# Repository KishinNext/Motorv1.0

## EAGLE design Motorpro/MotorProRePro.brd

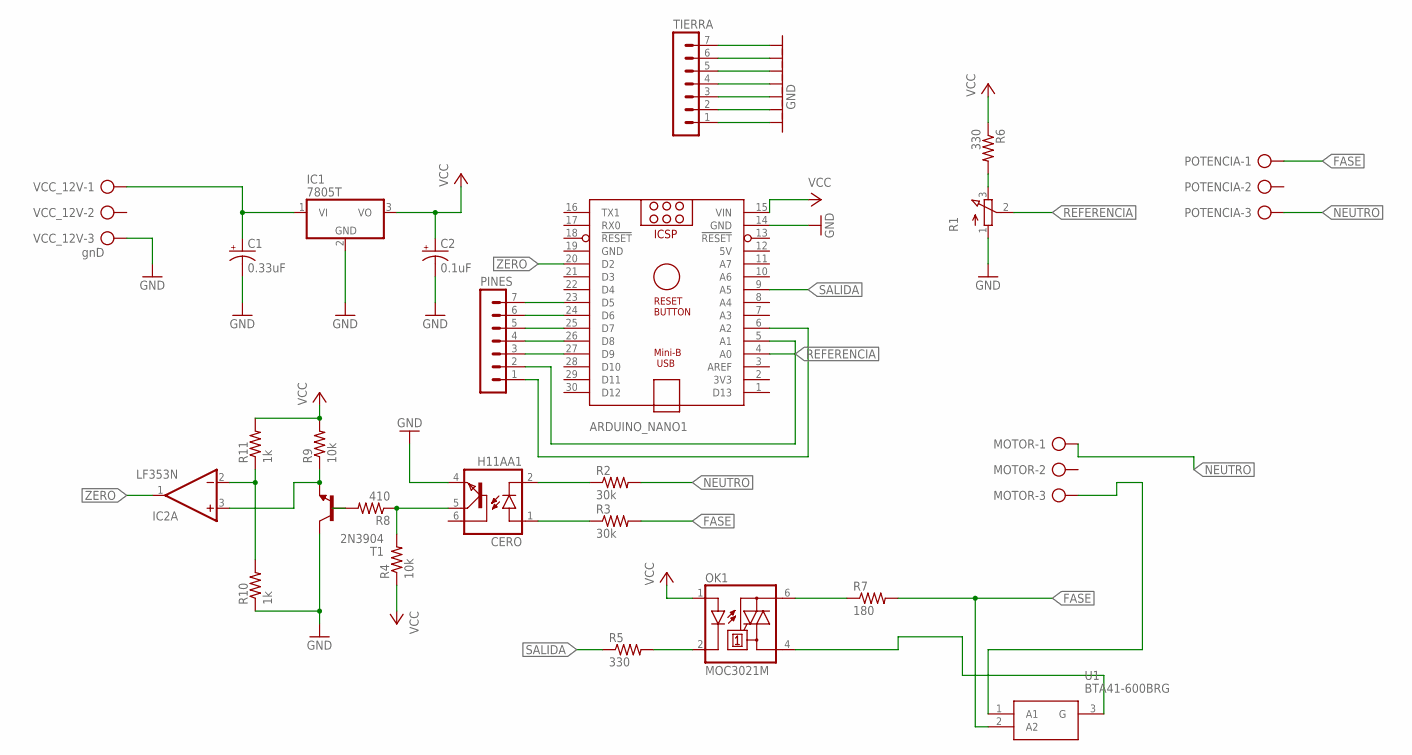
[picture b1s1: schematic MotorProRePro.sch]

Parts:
ARDUINO_NANO1: ARDUINO_NANO
C1: 0.33uF; E5-6
C2: 0.1uF; E5-6
CERO: H11AA1; DIL06
IC1: 7805T; TO220H
IC2: LF353N; DIL08
MOTOR: AK500/3-H
OK1: MOC3021M; DIL06
PINES: MA07-1
POTENCIA: AK500/3-H
R1: 3RP/1610N
R2, R3: 30k; 0207/10
R4, R9: 10k; 0207/10
R5, R6: 330; 0207/10
R7: 180; 0207/10
R8: 410; 0207/10
R10, R11: 1k; 0207/10
T1: 2N3904; TO92
TIERRA: MA07-1
U1: BTA41-600BRG; TO552P460X1530X2985-3P
VCC_12V: gnD; AK500/3-H

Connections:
5V: ARDUINO_NANO1.12 (5V)
FASE: POTENCIA.1, R3.2, R7.2, U1.2 (A2)
GND: ARDUINO_NANO1.14 (GND), ARDUINO_NANO1.19 (GND), C1.-, C2.-, CERO.4 (EMI), IC1.2 (GND), R1.1 (A), R10.1, T1.1 (C), TIERRA.1, TIERRA.2, TIERRA.3, TIERRA.4, TIERRA.5, TIERRA.6, TIERRA.7, VCC_12V.3
unnamed: C1.+, IC1.1 (VI), VCC_12V.1
unnamed: CERO.2 (C), R2.1
unnamed: CERO.1 (A), R3.1
unnamed: OK1.2 (C), R5.2
unnamed: R1.3 (E), R6.2
unnamed: OK1.6 (A2), R7.1
unnamed: MOTOR.3, U1.1 (A1)
unnamed: OK1.4 (A1), U1.3 (G)
unnamed: ARDUINO_NANO1.23 (D5), PINES.7
unnamed: ARDUINO_NANO1.24 (D6), PINES.6
unnamed: ARDUINO_NANO1.25 (D7), PINES.5
unnamed: ARDUINO_NANO1.26 (D8), PINES.4
unnamed: ARDUINO_NANO1.27 (D9), PINES.3
unnamed: ARDUINO_NANO1.5 (A1), PINES.2
unnamed: ARDUINO_NANO1.6 (A2), PINES.1
unnamed: R8.2, T1.2 (B)
unnamed: IC2.3 (+IN), R9.1, T1.3 (E)
unnamed: IC2.2 (-IN), R10.2, R11.1
NEUTRO: MOTOR.1, POTENCIA.3, R2.2
REFERENCIA: ARDUINO_NANO1.4 (A0), R1.2 (S)
SALIDA: ARDUINO_NANO1.9 (A5), R5.1
V+: IC2.8 (V+)
V-: IC2.4 (V-)
VCC: ARDUINO_NANO1.15 (VIN), C2.+, IC1.3 (VO), OK1.1 (A), R4.1, R6.1, R9.2, R11.2
ZERO: ARDUINO_NANO1.20 (D2), CERO.5 (COL), IC2.1 (OUT), R4.2, R8.1

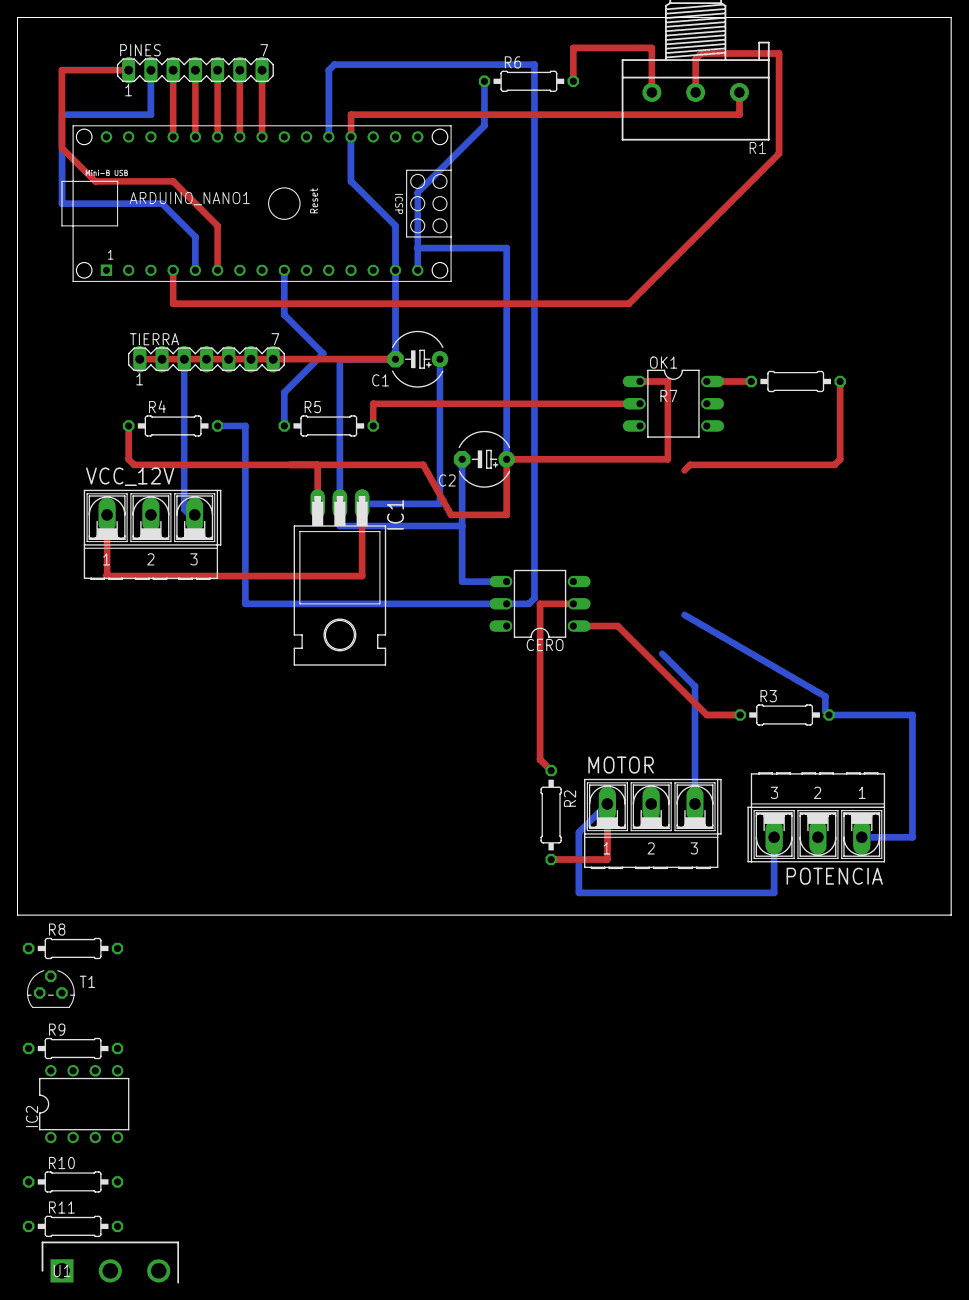
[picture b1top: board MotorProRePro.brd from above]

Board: 2 copper layers, 106.7 x 102.5 mm, 25 parts (0 on the bottom side), 25 nets.

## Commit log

2019-09-14 Version1.0 falta verificar en implementación
2019-09-17 Add files via upload
    final final
2019-09-18 Diseño de motor pro
2019-10-02 Board modificada
2019-10-06 Para eviar a china
2019-10-06 avance pcb y codigo final
